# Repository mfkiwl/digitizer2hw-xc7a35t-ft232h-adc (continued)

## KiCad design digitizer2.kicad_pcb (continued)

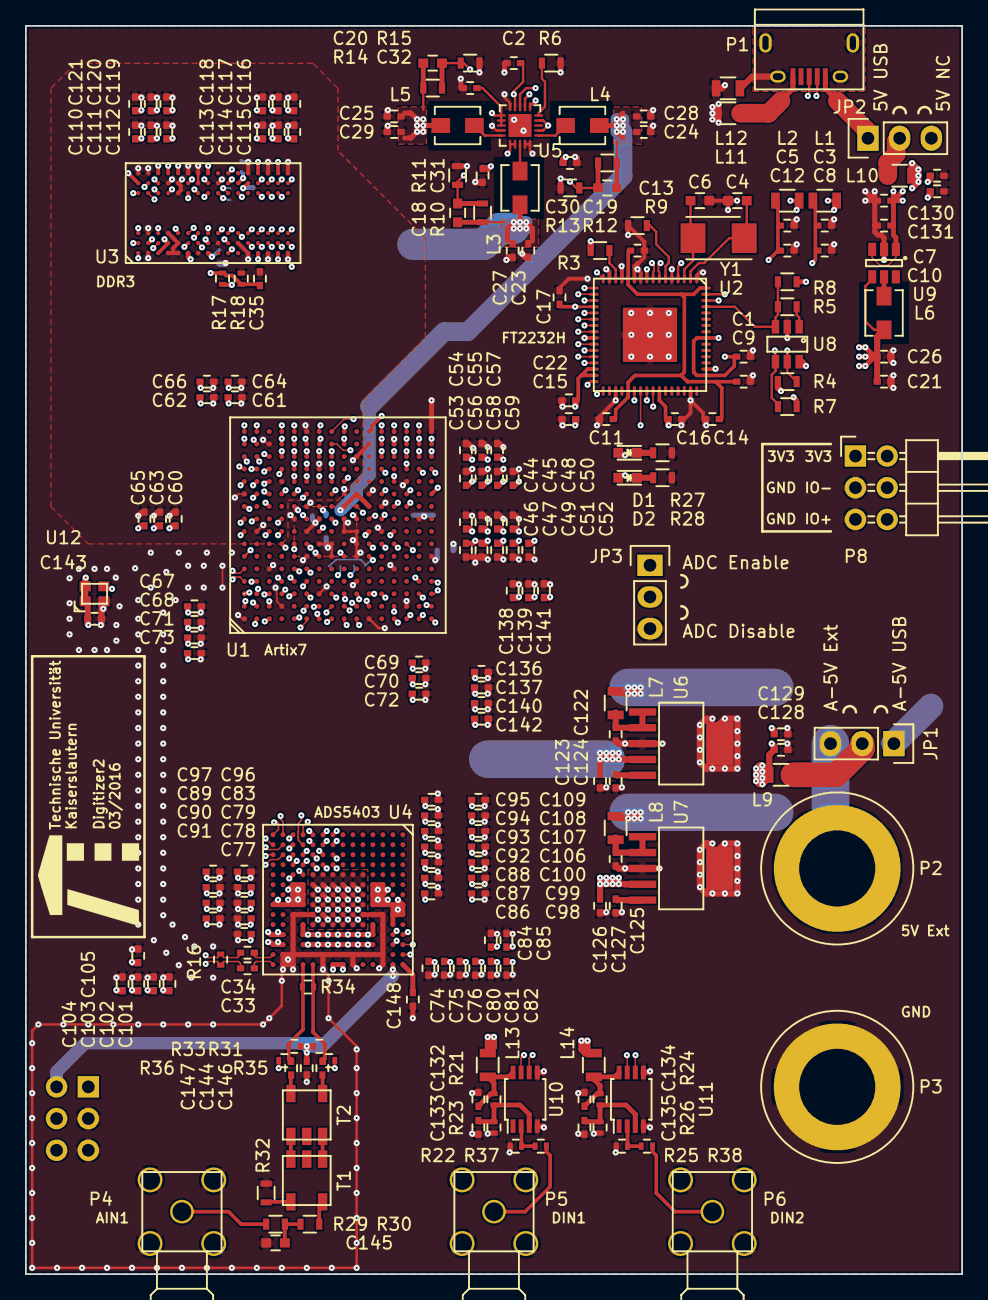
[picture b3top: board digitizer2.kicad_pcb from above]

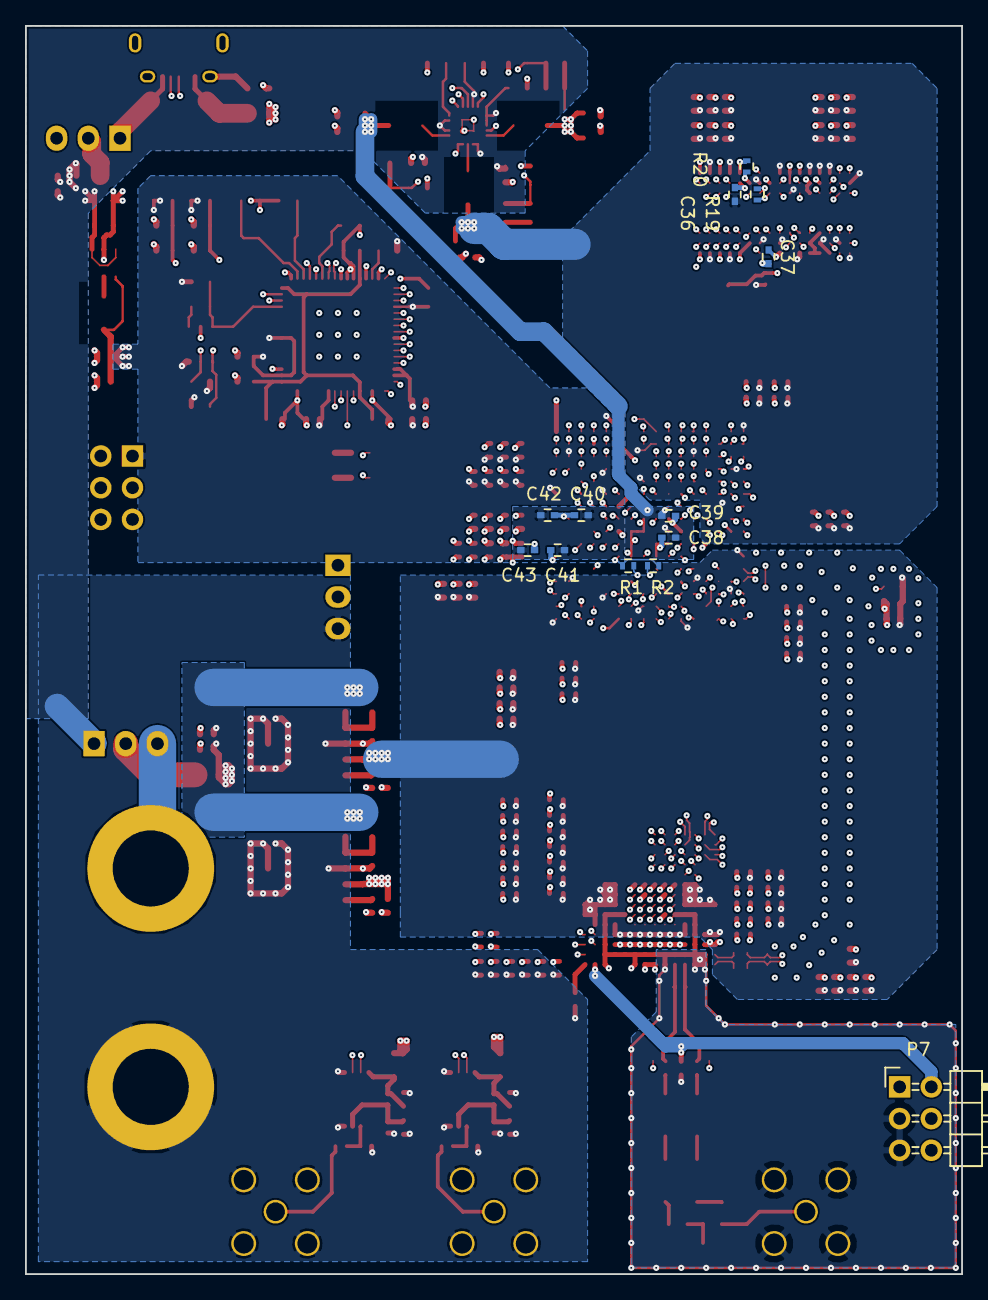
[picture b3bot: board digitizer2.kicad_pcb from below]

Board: 6 copper layers, 75.0 x 100.0 mm, 228 parts (13 on the bottom side), 177 nets.

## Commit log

2016-03-10 Initial routing
2016-03-10 Add FTDI footprint
2016-03-11 Tuned ADC DDR layout
2016-03-11 Changed LVDS layout. Try new DRAM position.
2016-03-14 Choose final DDR3 part (MT41K and MT41J pin compatible)
2016-03-14 Cleanup ADC routing
2016-03-15 DDR DQ lanes routing
2016-03-15 Finished DRAM DQ groups
2016-03-15 Begin DDR Addr/Ctrl tuning
2016-03-15 DRAM tuned
2016-03-15 Realign FTDI
2016-03-16 Layout FTDI interface
2016-03-16 Serial interfaces, cleanup
2016-03-16 Add ADC evaluation board documents, add usb tracks
2016-03-17 Power supply initial selection
2016-03-17 Config bank. Power labels
2016-03-17 Cleanup. Add Eeprom.
2016-03-18 Work on power supply
2016-03-18 Start routing power supply
2016-03-21 Power supply and bypass capacitors
2016-03-21 Prepare digital trigger and additional clock input
2016-03-21 Add more LVDS inputs and begin analog frontend
2016-03-21 Add SMA connectors
2016-03-22 First digitizer2 release candidate
2016-03-22 Add pads for input termination
2016-03-22 Fix DRC errors in schematic
2016-03-22 Edit top silk layer
2016-03-22 Add more GND fills
2016-03-22 Add TU KL logo
2016-03-22 Fix GND vias
2016-03-23 Cleanup, mark as revision 1.0
2016-03-23 Start adding order codes
2016-03-24 Replace 47uF footprints with 0805. Rev 1.1
2016-06-03 New power supply design (support pcb)
2016-06-04 Update Xilinx doc
2016-06-29 Board revision 1.2
2016-07-22 New capacitor selection
2016-07-22 Add 3.3V -> 2.5V regulator
2016-07-26 Move power supply off-board
2016-07-28 Last tweaks for board rev 1.2
2016-08-21 Add buck module project for new power supply
2016-11-02 Build new digitizer2-power board from buck module
2016-11-02 Update FTDI doc
2016-12-08 Fill in last details for power supply, cleanup
2016-12-23 Add missing kicad files
2016-12-23 Add license, update schema/pcb, add missing scripts
2017-03-07 Update USB symbol
